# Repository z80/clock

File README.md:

clock
=====

Shelа clock project

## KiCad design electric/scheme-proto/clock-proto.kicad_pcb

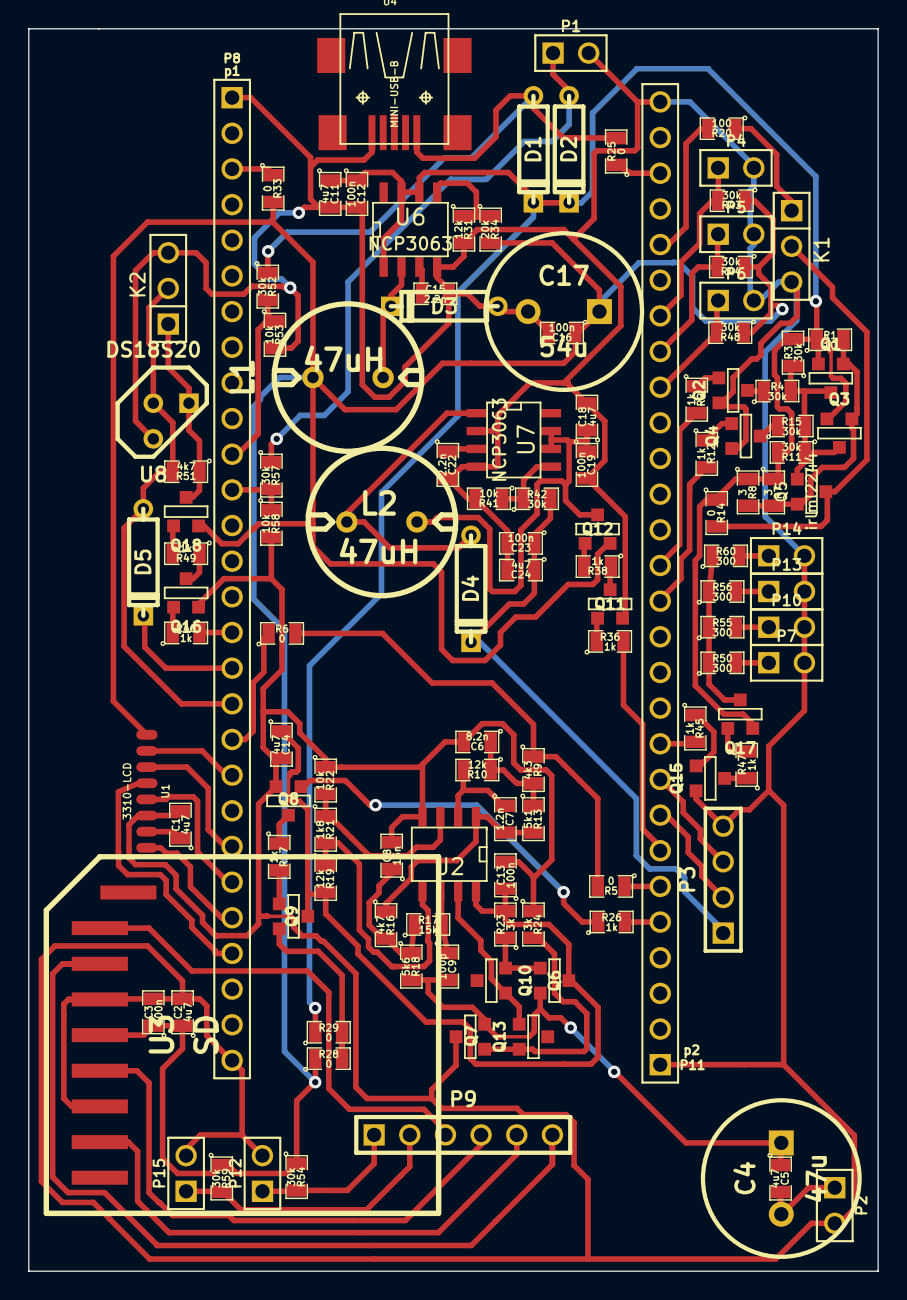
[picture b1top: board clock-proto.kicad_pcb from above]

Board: 2 copper layers, 60.5 x 88.5 mm, 123 parts (0 on the bottom side), 86 nets.

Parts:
C1, C2, C5, C11, C14, C18, C24: 4u7; SM0805
C3, C12, C13, C16, C19, C23: 100n; SM0805
C4: 47u; C2V10
C6: 8.2n; SM0805
C7: 1.2n; SM0805
C8: 15n; SM0805
C9: 100p; SM0805
C15, C22: 2.2n; SM0805
C17: 54u; C2V10
D1, D2, D3, D4, D5: 1N5819; D3
K1: servo; PIN_ARRAY_3X1
K2: 1-wire; PIN_ARRAY_3X1
L1, L2: 47uH; my_inductance
P1: batt; PIN_ARRAY_2X1
P2: speaker; PIN_ARRAY_2X1
P3: dist; PIN_ARRAY_4x1
P4: btn-1; PIN_ARRAY_2X1
P5: btn-2; PIN_ARRAY_2X1
P6: btn-3; PIN_ARRAY_2X1
P7, P10, P13, P14: led; PIN_ARRAY_2X1
P8: p1; PIN_ARRAY_28X1
P9: p3; PIN_ARRAY_6x1
P11: p2; PIN_ARRAY_28X1
P12: btn-4; PIN_ARRAY_2X1
P15: btn-5; PIN_ARRAY_2X1
Q1, Q3, Q7, Q9, Q10, Q12, Q17, Q18: bc857; SOT23EBC
Q2, Q4, Q6, Q8, Q11, Q13, Q15, Q16: bc847; SOT23EBC
Q5: irlml2244; SOT23GDS
R1: 10; SM0805
R2, R12, R26, R27, R36, R38, R45, R46, R47, R49: 1k; SM0805
R3, R4, R11, R15, R42, R43, R44, R48, R52, R54, R57, R59: 30k; SM0805
R5, R6, R14, R25, R28, R29, R33: 0; SM0805
R7, R8: 3; SM0805
R9: 4k3; SM0805
R10, R19, R31: 12k; SM0805
R13: 5k1; SM0805
R16, R51: 4k7; SM0805
R17: 15k; SM0805
R18: 5k6; SM0805
R20: 100; SM0805
R21: 1k8; SM0805
R22, R41, R53, R58: 10k; SM0805
R23, R24: 3k; SM0805
R34: 20k; SM0805
R50, R55, R56, R60: 300; SM0805
U1: 3310-LCD; my_nokia-3310-lcd
U2: AD8607_2; SO8E
U3: SD; sdc
U4: MINI-USB-B; my-mini-usb-b
U6, U7: NCP3063; SO8E
U8: DS18S20; TO92-123

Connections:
/1w-en: P8.16, R46.2
/1w-rx: D5.1, K2.2, P8.18, R51.2, U8.2
/1w-tx: D5.2, P8.17
/3v3: P8.3, R33.1
/5v: C23.1, C24.1, D4.2, P3.1, R42.2
/5v-en: P11.7, R36.2
/adapter-volt: P8.11, R52.2, R53.1
/amp-en: P11.5, R26.2
/battery-volt: P8.12, R57.2, R58.1
/btn-1: P4.1, P11.22, R43.2
/btn-2: P5.1, P11.21, R44.2
/btn-3: P6.1, P11.20, R48.2
/btn-4: P9.1, P12.1, R54.2
/btn-5: P9.2, P15.1, R59.2
/dist-echo: P3.3, P11.9
/dist-trig: P3.2, P11.8
/from-adapter: D1.1, R25.2, R52.1, U4.1
/from-battery: D2.1, P1.1, R57.1
/from-discovery-5v: P11.26, R25.1
/gate: Q1.3, Q3.3, Q5.G, R3.1, R4.2, R11.1, R15.2
/lcd-clk: P8.20, U1.2
/lcd-cs: P8.23, U1.5
/lcd-mode: P8.25, U1.4
/lcd-mosi: P8.22, U1.3
/lcd-rst: P8.24, U1.8
/led-en: P11.10, R45.2
/opamp-vcc: C13.1, C14.1, Q6.3, Q9.3, R19.2, R23.2, U2.8
/pa4: P8.19, R6.1
/pa8: P11.6, R5.1
/pb8: P11.24, R20.2
/pb12: P9.3, U3.1
/pb13: P9.4, U3.5
/pb14: P9.5, U3.7
/pb15: P9.6, U3.2
/pc10: P11.14, R12.2
/pc11: P11.15, R2.2
/power: C11.1, C12.1, D1.2, D2.2, Q1.1, Q3.1, Q17.1, R1.1, R3.2, R7.1, R8.1, R11.2, R14.1, R29.1, U6.1, U6.6, U6.7
/ref_3v3: R21.1, R22.2, U2.3
/ref_5v: R19.1, R21.2, U2.5
/servo-vcc: K1.2, Q5.D, R14.2
/speaker-1: C4.2, C5.2, P2.1
/src: Q1.2, Q3.2, Q5.S, R1.2, R7.2, R8.2
GND: C1.2, C2.2, C3.2, C6.2, C8.2, C11.2, C12.2, C13.2, C14.2, C15.2, C16.2, C17.2, C18.2, C19.2, C22.2, C23.2, C24.2, D3.1, K1.3, K2.3, P1.2, P2.2, P3.4, P4.2, P5.2, P6.2, P7.2, P8.1, P8.28, P10.2, P11.1, P11.28, P12.2, P13.2, P14.2, P15.2, Q2.1, Q4.1, Q7.3, Q8.1, Q11.1, Q15.1, Q16.1, R22.1, R24.1, R31.2, R41.2, R53.2, R58.2, U1.6, U2.4, U3.3, U3.6, U4.5, U6.4, U7.2, U7.4, U8.1
unnamed: Q15.2, R45.1
unnamed: P7.1, R50.2
unnamed: Q15.3, R47.1
unnamed: Q17.2, R47.2
unnamed: P13.1, R56.2
unnamed: P10.1, R55.2
unnamed: Q17.3, R50.1, R55.1, R56.1, R60.1
unnamed: P14.1, R60.2
unnamed: Q16.2, R46.1
unnamed: Q16.3, R49.1
unnamed: Q18.2, R49.2
unnamed: K2.1, Q18.3, R51.1, U8.3
unnamed: C7.1, R10.2, U2.2
unnamed: C7.2, R13.2, R16.1, U2.1
unnamed: C8.1, R16.2, R17.1, R18.1
unnamed: C6.1, R9.2, R10.1, R13.1
unnamed: Q10.2, Q13.2, U2.7
unnamed: C9.1, R17.2, U2.6
unnamed: Q7.2, Q13.1, R24.2
unnamed: Q6.2, Q10.1, R23.1
unnamed: Q8.2, R26.1
unnamed: Q8.3, R27.1
unnamed: Q9.2, R27.2
unnamed: Q9.1, R28.2, R29.2
unnamed: C1.1, U1.7
unnamed: C4.1, C5.1, C9.2, Q6.1, Q7.1, R18.2
unnamed: C18.1, C19.1, L2.1, Q12.3, U7.6, U7.7
unnamed: R5.2, R6.2, R9.1
unnamed: C22.1, U7.3
unnamed: D4.1, L2.2, U7.1
unnamed: Q4.2, R12.1
unnamed: Q4.3, R15.1
unnamed: Q2.3, R4.1
unnamed: Q2.2, R2.1
unnamed: R41.1, R42.1, U7.5
unnamed: D3.2, L1.1, U6.2
unnamed: R31.1, R34.1, U6.5
unnamed: C15.1, U6.3
unnamed: K1.1, R20.1
unnamed: Q12.2, R38.2
unnamed: Q11.2, R36.1
unnamed: Q11.3, R38.1
VDD: C2.1, C3.1, C16.1, C17.1, L1.2, Q12.1, Q18.1, R28.1, R33.2, R34.2, R43.1, R44.1, R48.1, R54.1, R59.1, U1.1, U3.4

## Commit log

2014-02-12 Added temporary folder exclusion.
2014-02-12 Component libraries.
2014-02-12 Analyzing circuit...
2014-02-13 Moved docs to an appropriate folder.
2014-02-13 Added examples to base project on.
2014-02-13 MCU docs.
2014-02-13 Added PDF with pinout.
2014-02-13 2 channel amplifier.
2014-02-14 Mass storage based bootloader.
2014-02-14 Added chibios and projects.
2014-02-14 STM32F105RCT6
2014-02-15 Calculated elements for sound filter.
2014-02-15 Started clock prototype board.
2014-02-16 stm32vldiscovery
2014-02-16 Designing clock-proto.
2014-02-16 Drawing scheme.
2014-02-16 Made circuit. Supposed to add a few LEDs to provide LCD back light
2014-02-17 Designing circuit...
2014-02-18 Making scheme.
2014-02-18 Connecte wires to sockets.
2014-02-18 3310 LCD should be fixed. All pins are of power_in type.
2014-02-21 Designing the circuit.
2014-02-21 Placing components.
2014-02-22 Placing elements...
2014-02-23 Placing components and routing wires.
2014-02-24 Placing elements and routing...
2014-02-25 Routing...
2014-03-02 Finished routing.
2014-03-03 Components list without unnecessary ones.
2014-03-06 Shifted horizontal socket a bit upwards because, it didn't match the one on Disccovery board.
2014-03-06 KiCad libraries were not saved due to this issue.
2014-03-08 Added all libraries with components.
2014-03-08 Radically simplified audio scheme.
2014-03-10 Remade amplifier scheme and rerouted the whole scheme respectively.
2014-03-10 Recalculated values for 12kHz low pass filter.
2014-03-12 Started firmware design. Implementing playback...
2014-03-13 Unpacked FatFS.
2014-03-13 Made playback.c compilable.
2014-03-13 adpcm encoder and decoder.
2014-03-15 Started 3310 LCD support.
2014-03-15 Adjusting 3310 to Chibios.
2014-03-15 3310 support compiles.
2014-03-16 Compiles with files included.
2014-03-17 Debugging SD SPI io. It doesn't work.
2014-03-17 Added FAT test project.
2014-03-17 Debugging...
2014-03-17 LCD also doesn't work.
2014-03-17 Debugging. Nothing work at the moment.
2014-03-17 Got old project with filesystem which worked with this SD card.
2014-03-17 LCD pinout. Looks like routed and soldered properly.
2014-03-17 Just compiled old file.
2014-03-17 Adjusted project.
2014-03-17 SD card doesn't work. Driver expects FF but gets 0. I'm going to solder pullups.
2014-03-18 Replaced with different test project.
2014-03-18 Commented out GPIO initializers.
2014-03-19 Trying to revert...
2014-03-19 Revert "Just compiled old file."
    This reverts commit b886b3fa96096836dc1765796f663618c6a8a014.
    Conflicts:
    firmware/firmware/debug_ext.sh
    firmware/firmware/flash.sh
2014-03-19 Mass storage as is.
2014-03-19 And now it works. Decreased memory consumption.
2014-03-20 Prepared project for SD card support adjustment.
2014-03-21 Filling diskio routines.
2014-03-22 Filling procedures.
2014-03-23 FatFS compiles.
2014-03-23 Minimizing memory usage.
2014-03-23 wait_ready() return 0xFF which indicates that there is no response from SD card.
2014-03-23 By getting Martin Thomas's SD over SPI implementation I made it working.
2014-03-23 Copied prepared drivers for sound and screen.
2014-03-23 File content reading works.
2014-03-24 Playback works. But it is very silent.
2014-03-24 Fraction to width doesn't help to increase sound loudness.
2014-03-24 Turning the filter on helps a lot :)
2014-03-26 With LCD on sound playback hangs up in a few seconds after start.
2014-03-26 Working on LCD display.
2014-03-26 Returned CMSIS LCD implementation.
2014-03-26 Changed loop type.
2014-03-27 Designing LCD support.
2014-03-27 Refreshed lcd3310. But didn't assign PAD directions.
2014-03-28 LCD works simultaneously with sound.
2014-03-29 Editing clock project.
2014-03-30 Editing display source.
2014-03-31 Pyroelectric sensors. But these are too expensive. Much better are assembles at e-bay for less then 2$ each.
2014-03-31 Clock display works.
2014-03-31 Editing display functions.
2014-04-05 Working on buttons...
2014-04-20 Started servo control.
2014-04-21 Servo processing.
2014-04-27 Left only servo for testing.
2014-04-27 Debugging servo. Servo itself moves. But ranges are wrong.
2014-04-27 Debugging servo.
2014-05-02 It looks like servo works properly.
2014-05-02 Linear servo works correctly when there is a pause at the end of movement before turning control pulses off.
2014-05-02 With acceleration it also works. But it looks like there is a problem in servo itself. It has a position when movement is blocked. And it causes the porblems with positioning. But it is less sensible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
2014-05-02 Linear servo movement mode.
2014-05-05 Added media.
2014-05-14 Processed with "Fade In" and "Fade Out" filters.
2014-05-16 Implemented triggering.
2014-05-16 Prepared raw sounds for SD card.
2014-05-18 Works but without deep sleep mode.
